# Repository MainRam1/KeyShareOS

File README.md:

# KeyShare

An open-source 9-key programmable macropad built from the ground up — custom PCB designed in KiCad, CircuitPython firmware running on the RP2040, and a native macOS companion app written in Swift. Assign keyboard shortcuts, launch apps, type text, switch desktops, control media, open URLs, trigger app menu actions, or chain actions into multi-step macros — all from a compact 3x3 mechanical key grid that auto-switches profiles based on your active application or website.

## Features

- **8 action types** -- keyboard shortcuts, app launch, text typing, desktop switching, media control, open url, app menu actions, multi-step macros
- **Unlimited profiles** -- organize keys by task or project
- **Auto-switch by app** -- profiles change automatically based on the active application
- **Auto-switch by website** -- profiles change based on the active tab in Safari or Chrome
- **App menu actions** -- browse and trigger any menu bar item in any running app, with keyboard shortcut fallback
- **Visual key editor** -- drag-and-drop 3x3 grid in the preferences window
- **OSD overlay** -- on-screen display when the active profile changes
- **Menu bar utility** -- lives in the menu bar with no Dock icon
- **Hot-plug support** -- detects device connect/disconnect and recovers after sleep
- **Config file watching** -- edits made in a text editor are picked up immediately
- **Profile import/export** -- share profiles as JSON files
- **Custom PCB** -- open-source KiCad design with manufacturing-ready Gerber files

## How It Works

Press a Cherry MX key on the macropad → the RP2040 firmware sends a JSON message over USB serial → the macOS menu bar app receives it and executes the configured action. The app monitors your active application and browser tab, automatically switching profiles so your keys always match what you're working in. A bidirectional serial protocol handles device detection, hot-plug recovery, and sleep/wake reconnection.

## Requirements

| Component | Minimum |
|-----------|---------|
| macOS | 13.0 (Ventura) |
| Microcontroller | Raspberry Pi Pico (RP2040) |
| Switches | 9 x Cherry MX compatible |
| Firmware runtime | CircuitPython 9.x |

## Hardware

The `Hardware/` directory contains the complete KiCad project for a custom 2-layer PCB:

- **Schematic & PCB layout** -- KiCad 9.0 project files
- **Gerber files** -- manufacturing-ready, located in `Hardware/Gerbers/`
- **BOM** -- `Hardware/MacroPad.csv` with all components listed

Key components: RP2040 microcontroller, W25Q16 16Mbit SPI flash, USB-C connector with ESD protection, AP2112K-3.3 voltage regulator, and 9 Cherry MX compatible switch footprints.

## Quick Start

1. **Flash firmware** -- install [CircuitPython 9.x](https://circuitpython.org/board/raspberry_pi_pico/) on the Pico, then copy `firmware/code.py` and `firmware/boot.py` to the `CIRCUITPY` drive.
2. **Download the app** -- grab the latest `.zip` from [GitHub Releases](../../releases), unzip, and move `KeyShare.app` to `/Applications`.
3. **Launch** -- open the app. It appears in the menu bar.
4. **Grant Accessibility permission** -- the first-launch onboarding will prompt you. Go to **System Settings > Privacy & Security > Accessibility** and enable KeyShare.
5. **Plug in the macropad** -- the app detects it automatically.

## Building from Source

```bash
# Install xcodegen (once)
brew install xcodegen

# Generate the Xcode project
cd MacroApp
xcodegen generate

# Build
xcodebuild -project KeyShare.xcodeproj -scheme KeyShare -configuration Release build
```

The built `.app` bundle is ad-hoc signed -- no Apple Developer ID required.

## Firmware Setup

1. Hold the BOOTSEL button on the Pico and plug it in via USB.
2. Copy the CircuitPython 9.x `.uf2` file to the `RPI-RP2` drive.
3. After the Pico reboots, copy the firmware files:

```bash
cp firmware/code.py /Volumes/CIRCUITPY/
cp firmware/boot.py /Volumes/CIRCUITPY/
```

The Pico will reboot and begin communicating over USB serial.

## Configuration

The app stores its config at:

```
~/Library/Application Support/KeyShare/config.json
```

You can edit profiles and key bindings through the preferences window or by editing the JSON file directly. Changes are picked up automatically.

## License

[MIT](LICENSE)

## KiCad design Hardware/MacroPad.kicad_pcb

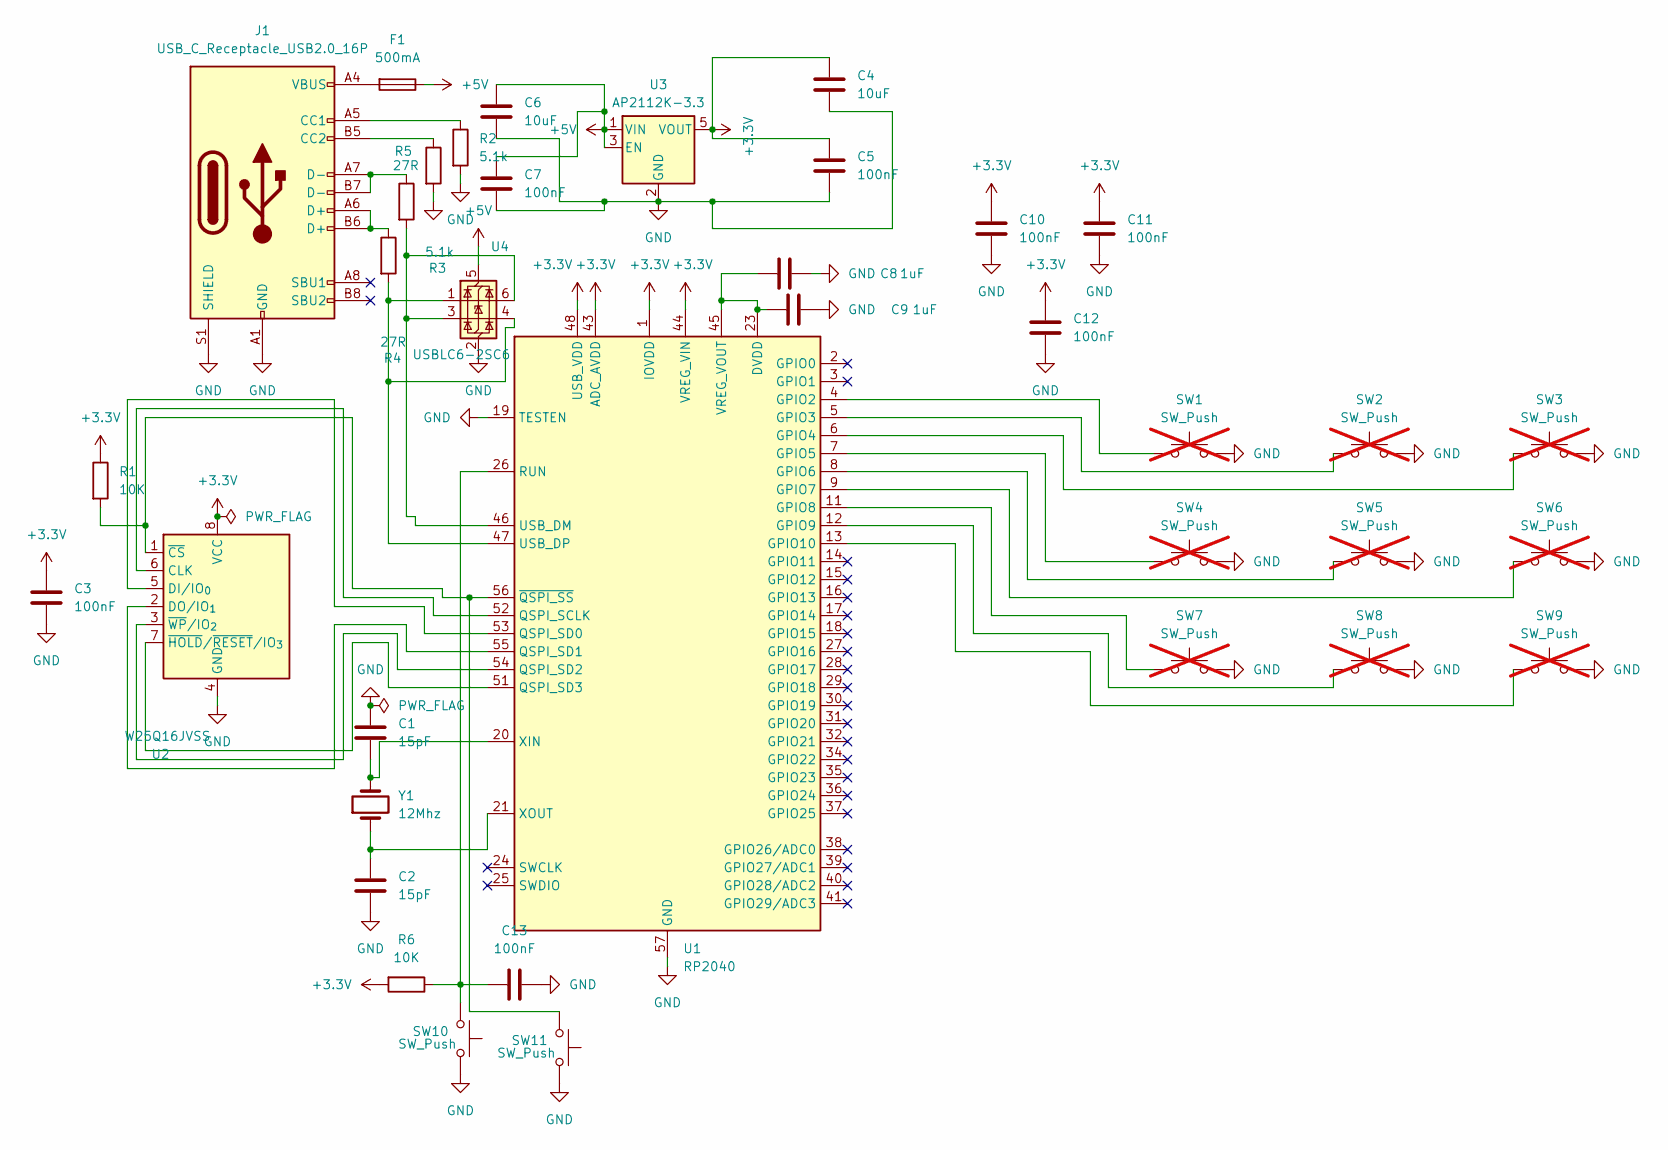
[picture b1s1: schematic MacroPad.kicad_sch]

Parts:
C1, C2: 15pF; C_0402_1005Metric; MPN GRM1555C1H150JA01D
C3, C5, C7, C10, C11, C12, C13: 100nF; C_0402_1005Metric; MPN CL05B104KO5NNNC
C4, C6: 10uF; C_0805_2012Metric; MPN CL21A106KAYNNNE
C8, C9: 1uF; C_0402_1005Metric; MPN CL05A105KA5NQNC
F1: 500mA; Fuse_1206_3216Metric; MPN 1206L050YR
J1: USB_C_Receptacle_USB2.0_16P; USB_C_Receptacle_GCT_USB4085; MPN USB4085-GF-A
R1, R6: 10K; R_0402_1005Metric; MPN RC0402FR-0710KL
R2, R3: 5.1k; R_0402_1005Metric; MPN RC0402FR-075K1L
R4, R5: 27R; R_0402_1005Metric; MPN RC0402FR-0727RL
SW1, SW2, SW3, SW4, SW5, SW6, SW7, SW8, SW9: SW_Push; SW_Cherry_MX_1.00u_PCB; not fitted
SW10, SW11: SW_Push; SW_SPST_PTS810; MPN PTS810 SJK 250 SMTR LFS
U1: RP2040; QFN-56-1EP_7x7mm_P0.4mm_EP3.2x3.2mm; MPN SC0914(13)
U2: W25Q16JVSS; SOIC-8_5.3x5.3mm_P1.27mm; MPN W25Q16JVSSIQ
U3: AP2112K-3.3; SOT-23-5; MPN AP2112K-3.3TRG1
U4: USBLC6-2SC6; SOT-23-6; MPN USBLC6-2SC6
Y1: 12Mhz; Crystal_SMD_3225-4Pin_3.2x2.5mm; MPN ABM8-272-T3

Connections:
+3.3V: C3.1, C4.1, C5.1, C10.1, C11.1, C12.1, R1.1, R6.2, U1.1 (IOVDD), U1.10 (IOVDD), U1.22 (IOVDD), U1.33 (IOVDD), U1.42 (IOVDD), U1.43 (ADC_AVDD), U1.44 (VREG_VIN), U1.48 (USB_VDD), U1.49 (IOVDD), U2.8 (VCC), U3.5 (VOUT)
+5V: C6.1, C7.1, F1.1, U3.1 (VIN), U3.3 (EN), U4.5 (VBUS)
GND: C1.1, C2.2, C3.2, C4.2, C5.2, C6.2, C7.2, C8.1, C9.1, C10.2, C11.2, C12.2, C13.2, J1.A1 (GND), J1.A12 (GND), J1.B1 (GND), J1.B12 (GND), J1.S1 (SHIELD), R2.2, R3.2, SW1.2, SW2.2, SW3.2, SW4.2, SW5.2, SW6.2, SW7.2, SW8.2, SW9.2, SW10.2, SW11.2, U1.19 (TESTEN), U1.57 (GND), U2.4 (GND), U3.2 (GND), U4.2 (GND)
unnamed: F1.2, J1.A4 (VBUS), J1.A9 (VBUS), J1.B4 (VBUS), J1.B9 (VBUS)
unnamed: J1.A5 (CC1), R2.1
unnamed: J1.B5 (CC2), R3.1
unnamed: J1.A6 (D+), J1.B6 (D+), R4.1
unnamed: J1.A7 (D-), J1.B7 (D-), R5.1
unnamed: SW1.1, U1.4 (GPIO2)
unnamed: SW2.1, U1.5 (GPIO3)
unnamed: SW3.1, U1.6 (GPIO4)
unnamed: SW4.1, U1.7 (GPIO5)
unnamed: SW5.1, U1.8 (GPIO6)
unnamed: SW6.1, U1.9 (GPIO7)
unnamed: SW7.1, U1.11 (GPIO8)
unnamed: SW8.1, U1.12 (GPIO9)
unnamed: SW9.1, U1.13 (GPIO10)
unnamed: U1.52 (QSPI_SCLK), U2.6 (CLK)
unnamed: U1.53 (QSPI_SD0), U2.5 (DI/IO_{0})
unnamed: U1.55 (QSPI_SD1), U2.2 (DO/IO_{1})
unnamed: U1.54 (QSPI_SD2), U2.3 (~WP/IO_{2})
unnamed: U1.51 (QSPI_SD3), U2.7 (~HOLD/~RESET/IO_{3})
unnamed: C13.1, R6.1, SW10.1, U1.26 (RUN)
unnamed: R5.2, U1.46 (USB_DM), U4.3 (I/O2), U4.6 (I/O1)
unnamed: R4.2, U1.47 (USB_DP), U4.1 (I/O1), U4.4 (I/O2)
unnamed: C8.2, C9.2, U1.23 (DVDD), U1.45 (VREG_VOUT), U1.50 (DVDD)
unnamed: C1.2, U1.20 (XIN), Y1.2
unnamed: C2.1, U1.21 (XOUT), Y1.1
unnamed: R1.2, SW11.1, U1.56 (~QSPI_SS), U2.1 (~CS)

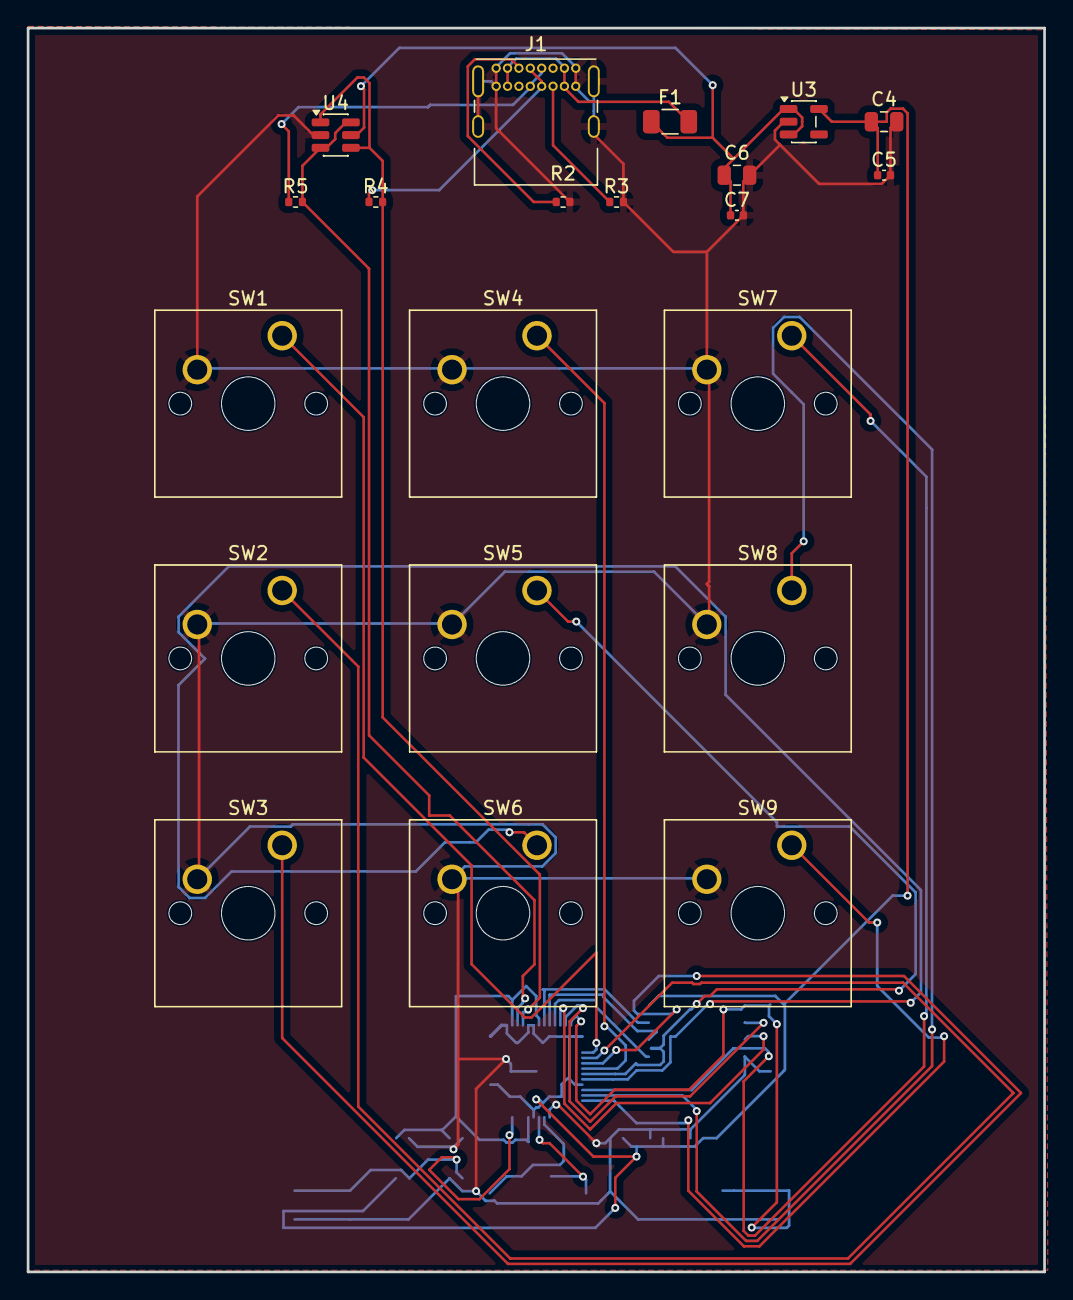
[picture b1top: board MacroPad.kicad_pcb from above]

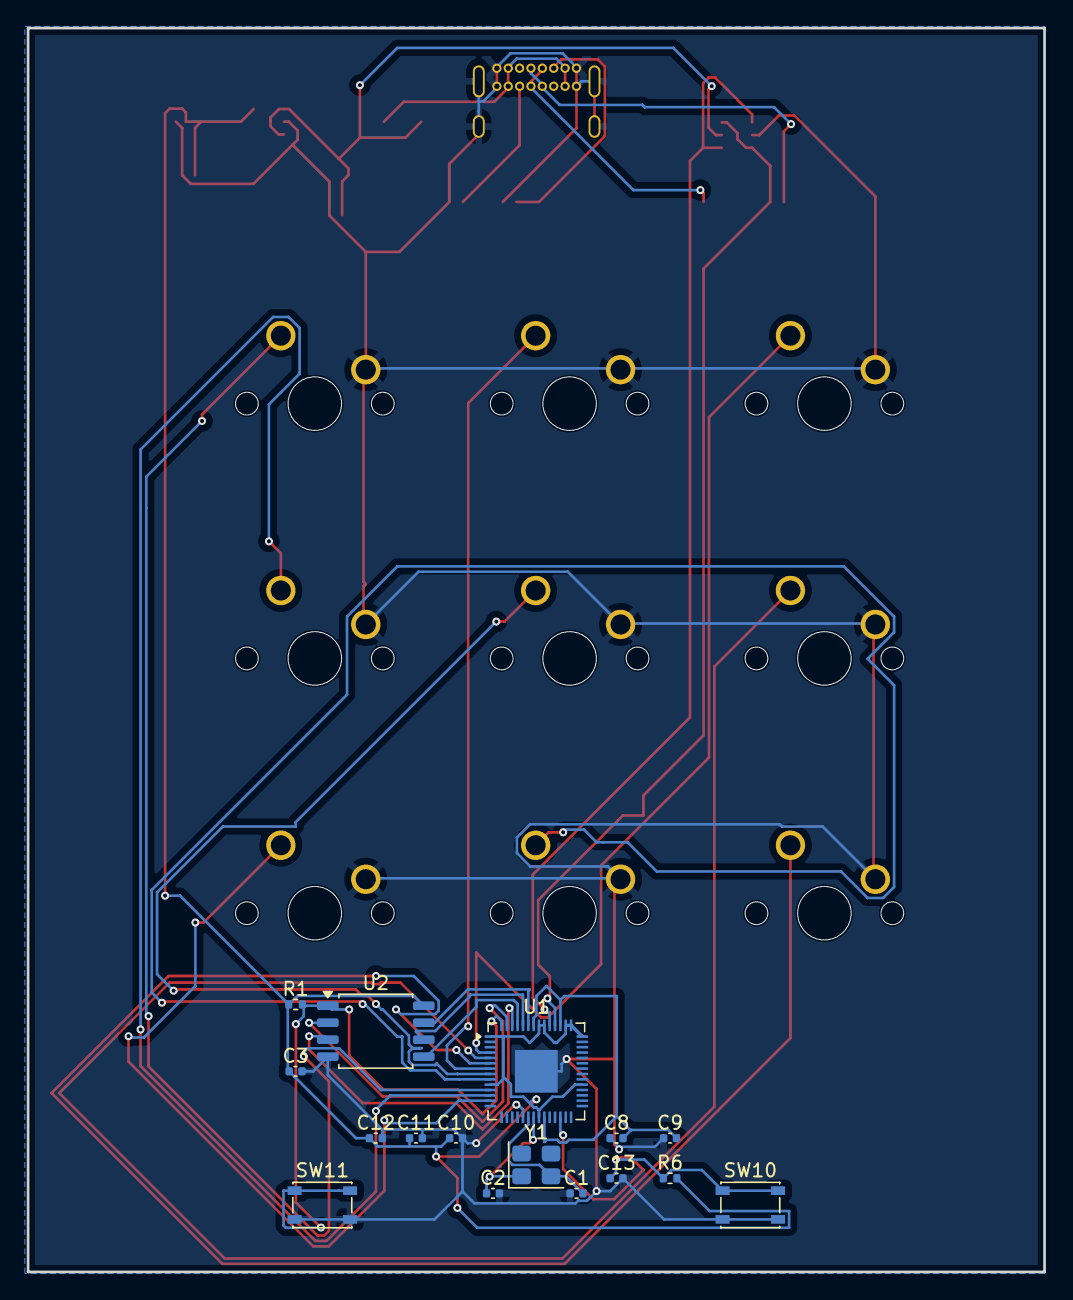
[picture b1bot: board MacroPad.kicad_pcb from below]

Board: 2 copper layers, 76.0 x 93.0 mm, 37 parts (16 on the bottom side), 29 nets.

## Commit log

2026-02-01 First commit of this project. Getting ready for the long road ahead and can't wait to get this thing up and running!
2026-02-02 Commit 2: Getting the Raspberry Pi Pico firmware ready
2026-02-03 Commit 3: Adding JSON fixtures for the serial protocol
2026-02-05 Commit 4: Basic MacOS Xcode setup
2026-02-07 Commit 5: Serial Communication Layer - discovery and message handling
2026-02-07 Commit 6: Serial protocol parsing tests for Swift and Python sides
2026-02-10 Commit 7: Action execution design
2026-02-11 Commit 8: All action types working!
2026-02-12 Commit 9: Tests for action execution and validation
2026-02-14 Commit 10: Config manager with JSON persistence
2026-02-15 Commit 11: Profile Switching and auto-switch
2026-02-18 Commit 12: Config test fixes and profile managers
2026-02-19 Commit 13: Sidebar Layout and status bar menu
2026-02-20 Commit 14: Key grid view and app picker
2026-02-22 Commit 15: Macro engine for multi-step actions
2026-02-24 Commit 16: Sleep/wake handling, OSD overlay, and onboarding
2026-02-26 Commit 17: Added tests
2026-02-28 Commit 18: Github actions CI and release
2026-03-01 Commit 19: App logo
2026-03-03 Commit 20: Guides
2026-03-03 Commit 21: Fixed Swiftlint
2026-03-03 Commit 22: fixed force try in serial protocol
2026-03-07 Commit 23: Open web url action type
2026-03-07 Commit 24: Update README.md
2026-03-07 Commit 25: Edit menu and keyboard shortcut support for text fields
2026-03-07 Commit 26: New Custom PCB
2026-03-07 Update README with project description, hardware section, and how it works
2026-03-08 Commit 27: New drag and drop/rename profile feature
2026-03-08 Commit 28: Fix swiftlint closure body length violations
2026-03-09 Commit 29: Fixed minor bug in the drap and drop feature for profiles
2026-03-09 Commit 30: Updated drag feature to work better
2026-03-16 Commit 31: profile auto-switch by website domain, menu-driven app actions
2026-03-16 Commit 32: Erros fixed
2026-03-16 Commit 33: fix trailing closure lint violation
2026-03-16 Commit 34: Description update
2026-03-22 Commit 35: Updated Schematic and PCB
